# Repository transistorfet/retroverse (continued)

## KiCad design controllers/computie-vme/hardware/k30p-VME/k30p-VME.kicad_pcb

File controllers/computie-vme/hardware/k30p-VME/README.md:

k30p-VME
========

Status: In Design

Latest: Unreleased

### About

A CPU card for a VME-based computer system using an MC68030 with some onboard RAM and Flash, and a
onboard serial ports with integrated FTDI Serial-to-USB controllers, and a programmable ATF1508
CPLD for glue logic.  The 'p' in the name stands for Programmable due to the CPLD.

Currently it's in development and I'm making slow progress with the CPLD, but I don't want to jump
further ahead until I'm sure I can make it work

Parts
-----

- MC68681
    - eBay, AliExpress, or other resellers are the only sources for these chips
- MC68030RC or MC68030RP:
    - eBay, AliExpress, or other resellers are the only sources for these chips

- 128-pin 13x13 PGA Socket
    - Phoenix Enterprise Connectors: https://www.peconnectors.com/sockets-pga-cpu-and-memory/hws4514/
    - Digikey: https://www.digikey.ca/en/products/detail/mill-max-manufacturing-corp/510-43-128-13-041001/7753825
    - Mouser: https://www.mouser.ca/ProductDetail/Aries-Electronics/128-PGM13039-10
    - (Not sure if correct pin arrangement) https://www.mouser.ca/ProductDetail/Preci-dip/510-87-128-13-041101

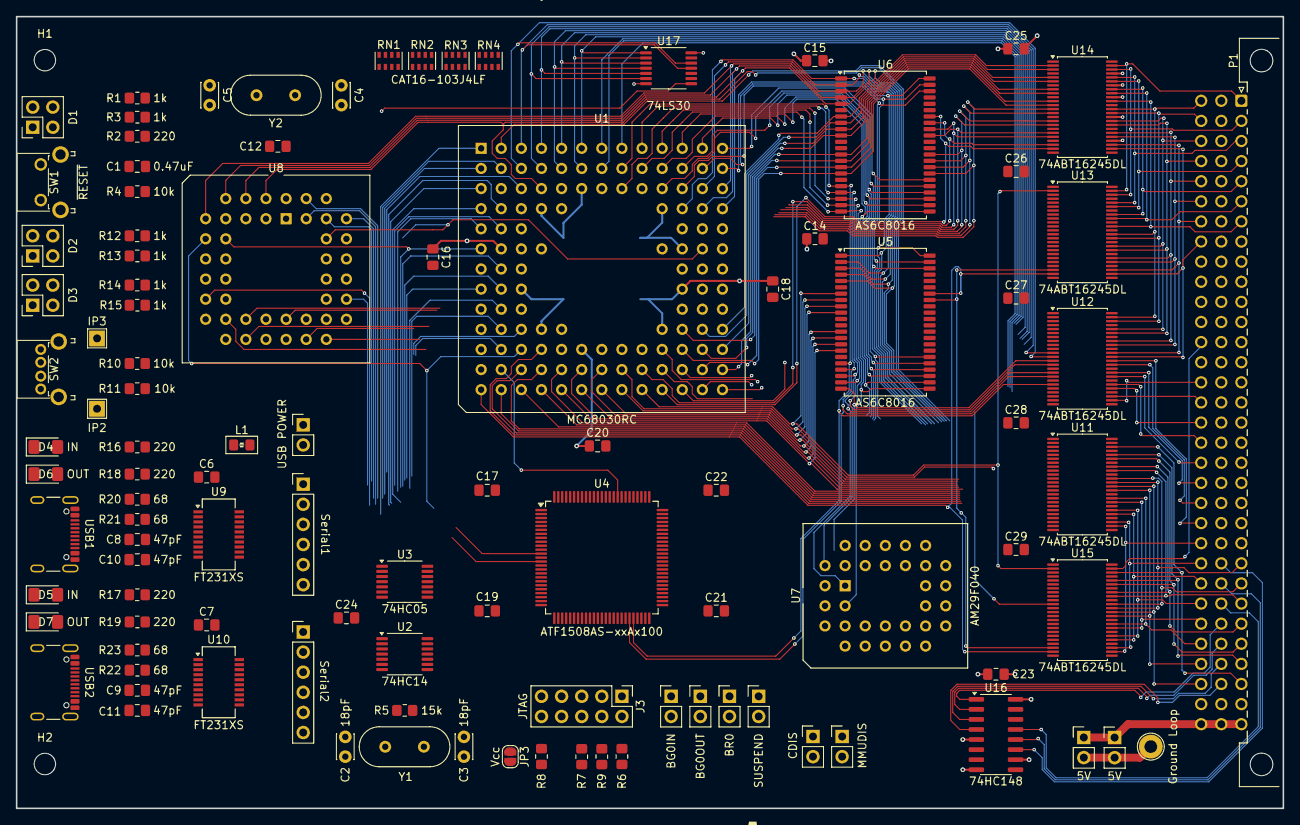
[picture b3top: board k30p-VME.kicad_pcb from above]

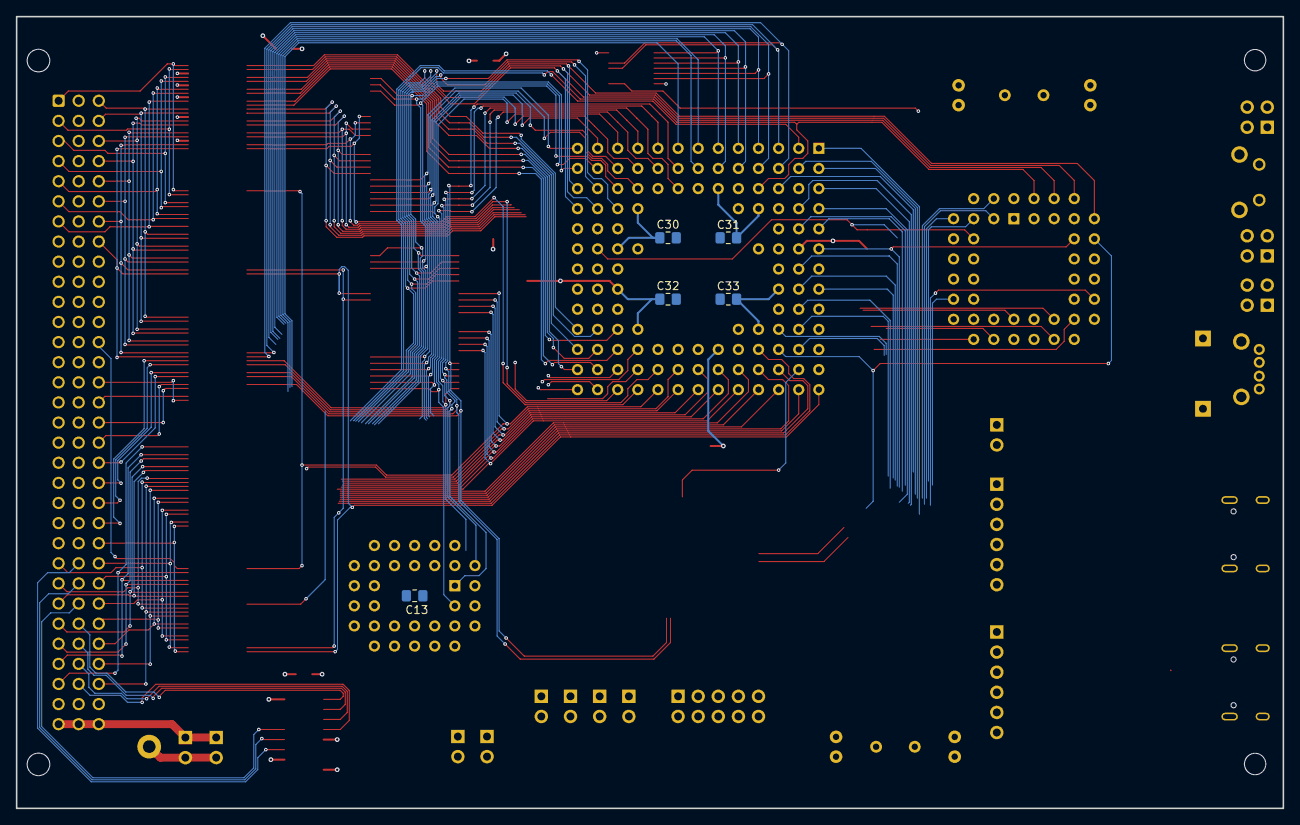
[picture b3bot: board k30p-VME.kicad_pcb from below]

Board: 4 copper layers, 160.0 x 100.0 mm, 111 parts (5 on the bottom side), 245 nets.

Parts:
C1: 0.47uF; C_0805_2012Metric_Pad1.18x1.45mm_HandSolder
C2, C3: 18pF; C_Disc_D3.0mm_W2.0mm_P2.50mm
C4: 15pF; C_Disc_D3.0mm_W2.0mm_P2.50mm
C5: 5pF; C_Disc_D3.0mm_W2.0mm_P2.50mm
C6, C7, C12, C13, C14, C15, C16, C17, C18, C19, C20, C21, C22, C23, C24, C25, C26, C27, C28, C29, C30, C31, C32, C33: 0.1uF; C_0805_2012Metric_Pad1.18x1.45mm_HandSolder
C8, C9, C10, C11: 47pF; C_0805_2012Metric_Pad1.18x1.45mm_HandSolder
D1: Harvatek HV-32H307B; Harvatek_HV-32312-260-2SUB
D2, D3: Harvatek HV-32312; Harvatek_HV-32312-260-2SUB
D4, D5: IN; LED_1206_3216Metric_Pad1.42x1.75mm_HandSolder
D6, D7: OUT; LED_1206_3216Metric_Pad1.42x1.75mm_HandSolder
H1, H2: MountingHole; MountingHole_2.7mm_M2.5_DIN965
J1, J2: 5V; PinHeader_1x02_P2.54mm_Vertical
J3: JTAG; PinHeader_2x05_P2.54mm_Vertical
J4: Serial1; PinHeader_1x06_P2.54mm_Vertical
J5: Serial2; PinHeader_1x06_P2.54mm_Vertical
JP1: CDIS; PinHeader_1x02_P2.54mm_Vertical
JP2: MMUDIS; PinHeader_1x02_P2.54mm_Vertical
JP3: Vcc; SolderJumper-2_P1.3mm_Open_RoundedPad1.0x1.5mm
JP4: USB POWER; PinHeader_1x02_P2.54mm_Vertical
JP5: BG0IN; PinHeader_1x02_P2.54mm_Vertical
JP6: BG0OUT; PinHeader_1x02_P2.54mm_Vertical
JP7: BR0; PinHeader_1x02_P2.54mm_Vertical
JP8: SUSPEND; PinHeader_1x02_P2.54mm_Vertical
L1: MI0805K601R-10; Ferrite_0805_2012Metric_Pad1.15x1.40mm_BigPads
P1: VME64-P1-3R; DIN41612_C_3x32_Male_Horizontal_THT
R1, R3, R12, R13, R14, R15: 1k; R_0805_2012Metric_Pad1.20x1.40mm_HandSolder
R2, R16, R17, R18, R19: 220; R_0805_2012Metric_Pad1.20x1.40mm_HandSolder
R4, R9, R10, R11: 10k; R_0805_2012Metric_Pad1.20x1.40mm_HandSolder
R5: 15k; R_0805_2012Metric_Pad1.20x1.40mm_HandSolder
R6, R7, R8: 4.7k; R_0805_2012Metric_Pad1.20x1.40mm_HandSolder
R20, R21, R22, R23: 68; R_0805_2012Metric_Pad1.20x1.40mm_HandSolder
RN1, RN2, RN3, RN4: CAT16-103J4LF; R_Cat16-4
S1: Logo_Open_Hardware_Small; OSHW-Symbol_6.7x6mm_SilkScreen
SW1: ~{RESET}; E-Switch_TL1105
SW2: E-Switch TL2243; E-Switch_TL2243
TP1: Ground Loop; TestPoint_Loop_D2.60mm_Drill1.6mm_Beaded
TP5: IP3; TestPoint_THTPad_2.0x2.0mm_Drill1.0mm
TP6: IP2; TestPoint_THTPad_2.0x2.0mm_Drill1.0mm
U1: MC68030RC; PGA-128_13x13_THT-Socket
U2: 74HC14; TSSOP-14_4.4x5mm_P0.65mm
U3: 74HC05; TSSOP-14_4.4x5mm_P0.65mm
U4: ATF1508AS-xxAx100; TQFP-100_14x14mm_P0.5mm
U5, U6: AS6C8016; TSOP-II-44_10.16x18.41mm_P0.8mm
U7: AM29F040; PLCC-32_THT-Socket
U8: MC68681; PLCC-44_THT-Socket
U9, U10: FT231XS; SSOP-20_3.9x8.7mm_P0.635mm
U11, U12, U13, U14, U15: 74ABT16245DL; TSSOP-48_6.1x12.5mm_P0.5mm
U16: 74HC148; SOIC-16_3.9x9.9mm_P1.27mm
U17: 74LS30; TSSOP-14_4.4x5mm_P0.65mm
USB1, USB2: USB_C_Plug_USB2.0; USB_C_Receptacle_GCT_USB4105-xx-A_16P_TopMnt_Horizontal
Y1, Y2: Crystal; Crystal_HC49-4H_Vertical

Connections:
+5V: C12.1, C13.1, C14.1, C15.1, C16.1, C17.1, C18.1, C19.1, C20.1, C21.1, C22.1, C23.1, C24.1, C25.1, C26.1, C27.1, C28.1, C29.1, C30.1, C31.1, C32.1, C33.1, J1.1, J2.1, JP3.2 (B), JP4.1 (A), P1.a32 (+5V), P1.b32 (+5V), P1.c32 (+5V), R1.2, R4.1, R6.1, R7.1, R8.1, R9.1, R12.2, R13.2, R14.2, R15.2, RN1.5 (R4.2), RN1.6 (R3.2), RN1.7 (R2.2), RN1.8 (R1.2), RN2.5 (R4.2), RN2.6 (R3.2), RN2.7 (R2.2), RN2.8 (R1.2), RN3.5 (R4.2), RN3.6 (R3.2), RN3.7 (R2.2), RN3.8 (R1.2), RN4.5 (R4.2), RN4.6 (R3.2), RN4.7 (R2.2), RN4.8 (R1.2), SW2.2 (D), SW2.4 (D), U1.C6 (VCC), U1.D4 (VCC), U1.D10 (VCC), U1.F2 (VCC), U1.F11 (VCC), U1.H3 (VCC), U1.H11 (VCC), U1.K4 (VCC), U1.K10 (VCC), U1.L6 (VCC), U2.14 (VCC), U3.14 (VCC), U4.3 (VCCIO), U4.18 (VCCIO), U4.34 (VCCIO), U4.39 (VCCINT), U4.51 (VCCIO), U4.66 (VCCIO), U4.82 (VCCIO), U4.91 (VCCINT), U5.11 (VCC), U5.33 (VCC), U6.11 (VCC), U6.33 (VCC), U7.32 (VCC), U8.44 (VCC), U9.15 (VCC), U10.15 (VCC), U11.7 (VCC), U11.18 (VCC), U11.31 (VCC), U11.42 (VCC), U12.7 (VCC), U12.18 (VCC), U12.31 (VCC), U12.42 (VCC), U13.7 (VCC), U13.18 (VCC), U13.31 (VCC), U13.42 (VCC), U14.7 (VCC), U14.18 (VCC), U14.31 (VCC), U14.42 (VCC), U15.7 (VCC), U15.18 (VCC), U15.31 (VCC), U15.42 (VCC), U16.16 (VCC), U17.14 (VCC)
CPU_CLK: U1.E1 (CLK), U4.83 (I/O)
D16X_DIR: U4.94 (I/O), U13.1 (DIR1), U13.24 (DIR2)
DL_DIR: U4.97 (I/O), U14.1 (DIR1), U14.24 (DIR2)
FC0: U1.D2 (FC0), U4.12 (I/O)
FC1: U1.C1 (FC1), U4.13 (I/O)
FC2: U1.D1 (FC2), U4.14 (I/O)
GND: C1.2, C2.2, C3.2, C4.1, C5.1, C6.2, C7.2, C8.2, C9.2, C10.2, C11.2, C12.2, C13.2, C14.2, C15.2, C16.2, C17.2, C18.2, C19.2, C20.2, C21.2, C22.2, C23.2, C24.2, C25.2, C26.2, C27.2, C28.2, C29.2, C30.2, C31.2, C32.2, C33.2, J1.2, J2.2, J3.2, J3.10, J4.6, J5.1, JP1.2 (B), JP2.2 (B), JP8.2 (B), P1.a9 (GND), P1.a11 (GND), P1.a15 (GND), P1.a17 (GND), P1.a19 (GND), P1.b20 (GND), P1.b23 (GND), P1.c9 (GND), R2.1, R3.1, R10.2, R11.2, SW1.1, TP1.1, U1.C5 (GND), U1.C7 (GND), U1.C9 (GND), U1.E3 (GND), U1.E11 (GND), U1.F3 (GND), U1.G3 (GND), U1.G11 (GND), U1.J3 (GND), U1.J11 (GND), U1.L5 (GND), U1.L7 (GND), U1.L8 (GND), U1.L9 (GND), U2.7 (GND), U3.7 (GND), U4.11 (GND), U4.26 (GND), U4.38 (GND), U4.43 (GND), U4.59 (GND), U4.74 (GND), U4.86 (GND), U4.95 (GND), U5.12 (VSS), U5.34 (VSS), U6.12 (VSS), U6.34 (VSS), U7.16 (GND), U8.22 (GND), U9.6 (GND), U9.16 (GND), U10.6 (GND), U10.16 (GND), U11.1 (DIR1), U11.4 (GND), U11.10 (GND), U11.15 (GND), U11.21 (GND), U11.24 (DIR2), U11.28 (GND), U11.34 (GND), U11.39 (GND), U11.45 (GND), U12.1 (DIR1), U12.4 (GND), U12.10 (GND), U12.15 (GND), U12.21 (GND), U12.24 (DIR2), U12.28 (GND), U12.34 (GND), U12.39 (GND), U12.45 (GND), U13.4 (GND), U13.10 (GND), U13.15 (GND), U13.21 (GND), U13.28 (GND), U13.34 (GND), U13.39 (GND), U13.45 (GND), U14.4 (GND), U14.10 (GND), U14.15 (GND), U14.21 (GND), U14.28 (GND), U14.34 (GND), U14.39 (GND), U14.45 (GND), U15.4 (GND), U15.10 (GND), U15.15 (GND), U15.21 (GND), U15.28 (GND), U15.34 (GND), U15.39 (GND), U15.45 (GND), U16.5 (EI), U16.8 (GND), U16.10 (IO), U17.7 (GND), USB1.A1 (GND), USB1.A12 (GND), USB1.B1 (GND), USB1.B12 (GND), USB1.S1 (SHIELD), USB2.A1 (GND), USB2.A12 (GND), USB2.B1 (GND), USB2.B12 (GND), USB2.S1 (SHIELD)
IP4: U4.54 (I/O), U8.43 (IP4)
IP5: U4.53 (I/O), U8.42 (IP5)
LA0: U1.A2 (A0), U4.35 (I/O), U7.12 (A0)
LA1: U1.C4 (A1), U4.36 (I/O), U7.11 (A1), U8.2 (RS1), U11.3 (B1)
LA2: U1.D13 (A2), U4.37 (I/O), U5.5 (A0), U6.5 (A0), U7.10 (A2), U8.4 (RS2), U11.5 (B2)
LA3: U1.D12 (A3), U4.40 (I/O), U5.4 (A1), U6.4 (A1), U7.9 (A3), U8.6 (RS3), U11.6 (B3)
LA4: U1.C13 (A4), U5.3 (A2), U6.3 (A2), U7.8 (A4), U8.7 (RS4), U11.8 (B4)
LA5: U1.C12 (A5), U5.2 (A3), U6.2 (A3), U7.7 (A5), U11.9 (B5)
LA6: U1.D11 (A6), U5.1 (A4), U6.1 (A4), U7.6 (A6), U11.11 (B6)
LA7: U1.B13 (A7), U5.44 (A5), U6.44 (A5), U7.5 (A7), U11.12 (B7)
LA8: U1.B12 (A8), U5.43 (A6), U6.43 (A6), U7.27 (A8), U11.13 (B8)
LA9: U1.C11 (A9), U5.42 (A7), U6.42 (A7), U7.26 (A9), U11.14 (B9)
LA10: U1.A13 (A10), U5.28 (A8), U6.28 (A8), U7.23 (A10), U11.16 (B10)
LA11: U1.C10 (A11), U5.27 (A9), U6.27 (A9), U7.25 (A11), U11.17 (B11)
LA12: U1.B11 (A12), U5.26 (A10), U6.26 (A10), U7.4 (A12), U11.19 (B12)
LA13: U1.A12 (A13), U5.25 (A11), U6.25 (A11), U7.28 (A13), U11.20 (B13)
LA14: U1.B10 (A14), U5.24 (A12), U6.24 (A12), U7.29 (A14), U11.22 (B14)
LA15: U1.A11 (A15), U5.23 (A13), U6.23 (A13), U7.3 (A15), U11.23 (B15)
LA16: U1.B9 (A16), U4.41 (I/O/PD2), U5.22 (A14), U6.22 (A14), U7.2 (A16), U12.13 (B8)
LA17: U1.A10 (A17), U4.42 (I/O), U5.21 (A15), U6.21 (A15), U7.30 (A17), U12.14 (B9)
LA18: U1.C8 (A18), U4.44 (I/O), U5.20 (A16), U6.20 (A16), U7.1 (A18), U12.16 (B10)
LA19: U1.A9 (A19), U4.45 (I/O), U5.19 (A17), U6.19 (A17), U12.17 (B11)
LA20: U1.B8 (A20), U4.46 (I/O), U5.18 (A18), U6.18 (A18), U12.19 (B12)
LA21: U1.A8 (A21), U4.47 (I/O), U12.20 (B13)
LA22: U1.B7 (A22), U4.48 (I/O), U12.22 (B14)
LA23: U1.A7 (A23), U4.49 (I/O), U12.23 (B15)
LA24: U1.A6 (A24), U12.2 (B0), U17.1
LA25: U1.B6 (A25), U12.3 (B1), U17.2
LA26: U1.A5 (A26), U12.5 (B2), U17.3
LA27: U1.B5 (A27), U12.6 (B3), U17.4
LA28: U1.A4 (A28), U12.8 (B4), U17.5
LA29: U1.B4 (A29), U12.9 (B5), U17.6
LA30: U1.A3 (A30), U12.11 (B6), U17.11
LA31: U1.B3 (A31), U12.12 (B7), U17.12
LD0: U1.K13 (D0), U6.7 (Q0), U14.2 (B0)
LD1: U1.K12 (D1), U6.8 (Q1), U14.3 (B1)
LD2: U1.L13 (D2), U6.9 (Q2), U14.5 (B2)
LD3: U1.M13 (D3), U6.10 (Q3), U14.6 (B3)
LD4: U1.L12 (D4), U6.13 (Q4), U14.8 (B4)
LD5: U1.K11 (D5), U6.14 (Q5), U14.9 (B5)
LD6: U1.M12 (D6), U6.15 (Q6), U14.11 (B6)
LD7: U1.L11 (D7), U6.16 (Q7), U14.12 (B7)
LD8: U1.N13 (D8), U6.29 (Q8), U14.13 (B8)
LD9: U1.M11 (D9), U6.30 (Q9), U14.14 (B9)
LD10: U1.L10 (D10), U6.31 (Q10), U14.16 (B10)
LD11: U1.N12 (D11), U6.32 (Q11), U14.17 (B11)
LD12: U1.M10 (D12), U6.35 (Q12), U14.19 (B12)
LD13: U1.N11 (D13), U6.36 (Q13), U14.20 (B13)
LD14: U1.M9 (D14), U6.37 (Q14), U14.22 (B14)
LD15: U1.N10 (D15), U6.38 (Q15), U14.23 (B15)
LD16: U1.N9 (D16), U5.7 (Q0), U13.2 (B0), U15.2 (B0)
LD17: U1.M8 (D17), U5.8 (Q1), U13.3 (B1), U15.3 (B1)
LD18: U1.N8 (D18), U5.9 (Q2), U13.5 (B2), U15.5 (B2)
LD19: U1.N7 (D19), U5.10 (Q3), U13.6 (B3), U15.6 (B3)
LD20: U1.M7 (D20), U5.13 (Q4), U13.8 (B4), U15.8 (B4)
LD21: U1.N6 (D21), U5.14 (Q5), U13.9 (B5), U15.9 (B5)
LD22: U1.M6 (D22), U5.15 (Q6), U13.11 (B6), U15.11 (B6)
LD23: U1.N5 (D23), U5.16 (Q7), U13.12 (B7), U15.12 (B7)
LD24: U1.M5 (D24), U5.29 (Q8), U7.13 (Q0), U8.28 (D0), U13.13 (B8), U15.13 (B8)
LD25: U1.N4 (D25), U5.30 (Q9), U7.14 (Q1), U8.18 (D1), U13.14 (B9), U15.14 (B9)
LD26: U1.N3 (D26), U5.31 (Q10), U7.15 (Q2), U8.27 (D2), U13.16 (B10), U15.16 (B10)
LD27: U1.M4 (D27), U5.32 (Q11), U7.17 (Q3), U8.19 (D3), U13.17 (B11), U15.17 (B11)
LD28: U1.N2 (D28), U5.35 (Q12), U7.18 (Q4), U8.26 (D4), U13.19 (B12), U15.19 (B12)
LD29: U1.M3 (D29), U5.36 (Q13), U7.19 (Q5), U8.20 (D5), U13.20 (B13), U15.20 (B13)
LD30: U1.L4 (D30), U5.37 (Q14), U7.20 (Q6), U8.25 (D6), U13.22 (B14), U15.22 (B14)
LD31: U1.N1 (D31), U5.38 (Q15), U7.21 (Q7), U8.21 (D7), U13.23 (B15), U15.23 (B15)
MAIN_CLK: U2.6, U4.87 (I/GCLK1)
MD32X_DIR: U4.92 (I/O), U15.1 (DIR1), U15.24 (DIR2)
unnamed: C1.1, R4.2, SW1.2, U2.13
unnamed: C2.1, R5.2, U2.3, Y1.1
unnamed: C3.1, R5.1, U2.4, U2.5, Y1.2
unnamed: D1.2 (K1), R3.2
unnamed: D1.4 (K2), R2.2
unnamed: D2.1 (A1), R13.1
unnamed: D2.3 (A2), R12.1
unnamed: D2.2 (K1), U8.16 (OP5)
unnamed: D2.4 (K2), U8.30 (OP4)
unnamed: D3.1 (A1), R15.1
unnamed: D3.3 (A2), R14.1
unnamed: D3.2 (K1), U8.17 (OP7)
unnamed: D3.4 (K2), U8.29 (OP6)
unnamed: D4.2 (A), R16.2
unnamed: D4.1 (K), U9.10 (CBUS2)
unnamed: D5.2 (A), R17.2
unnamed: D5.1 (K), U10.10 (CBUS2)
unnamed: D6.2 (A), R18.2
unnamed: D6.1 (K), U9.17 (CBUS1)
unnamed: D7.2 (A), R19.2
unnamed: D7.1 (K), U10.17 (CBUS1)
unnamed: J3.4, JP3.1 (A)
unnamed: JP4.2 (B), L1.2
unnamed: P1.a21 (~IACKIN), P1.a22 (~IACKOUT)
unnamed: P1.a20 (~IACK), U3.12
unnamed: P1.b30 (~IRQ1), U16.4 (I7)
unnamed: P1.b29 (~IRQ2), U16.3 (I6)
unnamed: P1.b28 (~IRQ3), U16.2 (I5)
unnamed: P1.b27 (~IRQ4), U16.1 (I4)
unnamed: P1.b26 (~IRQ5), U16.13 (I3)
unnamed: P1.b25 (~IRQ6), U16.12 (I2)
unnamed: P1.b24 (~IRQ7), U16.11 (I1)
unnamed: RN2.2 (R2.1), U1.G1 (STERM)
unnamed: RN2.3 (R3.1), U1.J1 (CBACK)
unnamed: RN2.4 (R4.1), U1.L1 (CIIN)
unnamed: R11.1, SW2.1 (C), TP6.1, U8.40 (IP2)
unnamed: R10.1, SW2.3 (C), TP5.1, U8.3 (IP3)
unnamed: U2.8, U3.9
unnamed: U2.12, U3.1, U3.3
unnamed: C4.2, U8.36 (X1/CLK), Y2.2
unnamed: C5.2, U8.37 (X2), Y2.1
unnamed: C6.1, R16.1, R18.1, U9.3 (VCCIO), U9.13 (3V3OUT), U9.14 (~RESET)
unnamed: R20.2, U9.12 (USBDM)
unnamed: R21.2, U9.11 (USBDP)
unnamed: C7.1, R17.1, R19.1, U10.3 (VCCIO), U10.13 (3V3OUT), U10.14 (~RESET)
unnamed: R22.2, U10.12 (USBDM)
unnamed: R23.2, U10.11 (USBDP)
unnamed: U4.50 (I/O), U17.8
OP2: U4.56 (I/O), U8.31 (OP2)
OP3: U4.55 (I/O), U8.15 (OP3)
SIZ0: U1.L2 (SIZ0), U4.5 (I/O)
SIZ1: U1.K3 (SIZ1), U4.6 (I/O)
STATUSLED: D1.3 (A2), U4.52 (I/O)
TCK: J3.1, R6.2, U4.62 (I/O/TCK)
TDI: J3.9, R8.2, U4.4 (I/O/TDI)
TDO: J3.3, R9.2, U4.73 (I/O/TDO)
TMS: J3.5, R7.2, U4.15 (I/O/TMS)
UART1_CTS: J4.5, U8.32 (OP0), U9.9 (~CTS)
UART1_DTR: J4.1, U8.8 (IP0), U9.1 (~DTR)
UART1_RX: J4.2, U8.33 (TXDA), U9.4 (RXD)
UART1_TX: J4.3, U8.35 (RXDA), U9.20 (TXD)
UART2_CTS: J5.2, U8.14 (OP1), U10.9 (~CTS)
UART2_DTR: J5.6, U8.5 (IP1), U10.1 (~DTR)
UART2_RX: J5.5, U8.13 (TXDB), U10.4 (RXD)
UART2_TX: J5.4, U8.11 (RXDB), U10.20 (TXD)
USB1_5V: J4.4, L1.1, USB1.A4 (VBUS), USB1.A9 (VBUS), USB1.B4 (VBUS), USB1.B9 (VBUS)
USB1_DN: C8.1, R20.1, USB1.A7 (D-)
USB1_DP: C10.1, R21.1, USB1.A6 (D+)
USB2_DN: C9.1, R22.1, USB2.A7 (D-)
USB2_DP: C11.1, R23.1, USB2.A6 (D+)
VA1: P1.a30 (A01), U11.46 (A1), U15.46 (A1)
VA2: P1.a29 (A02), U11.44 (A2), U15.44 (A2)
VA3: P1.a28 (A03), U11.43 (A3), U15.43 (A3)
VA4: P1.a27 (A04), U11.41 (A4), U15.41 (A4)
VA5: P1.a26 (A05), U11.40 (A5), U15.40 (A5)
VA6: P1.a25 (A06), U11.38 (A6), U15.38 (A6)
VA7: P1.a24 (A07), U11.37 (A7), U15.37 (A7)
VA8: P1.c30 (A8), U11.36 (A8), U15.36 (A8)
VA9: P1.c29 (A9), U11.35 (A9), U15.35 (A9)
VA10: P1.c28 (A10), U11.33 (A10), U15.33 (A10)
VA11: P1.c27 (A11), U11.32 (A11), U15.32 (A11)
VA12: P1.c26 (A12), U11.30 (A12), U15.30 (A12)
VA13: P1.c25 (A13), U11.29 (A13), U15.29 (A13)
VA14: P1.c24 (A14), U11.27 (A14), U15.27 (A14)
VA15: P1.c23 (A15), U11.26 (A15), U15.26 (A15)
VA16: P1.c22 (A16), U12.36 (A8)
VA17: P1.c21 (A17), U12.35 (A9)
VA18: P1.c20 (A18), U12.33 (A10)
VA19: P1.c19 (A19), U12.32 (A11)
VA20: P1.c18 (A20), U12.30 (A12)
VA21: P1.c17 (A21), U12.29 (A13)
VA22: P1.c16 (A22), U12.27 (A14)
VA23: P1.c15 (A23), U12.26 (A15)
VAM0: P1.b16 (AM0), U4.72 (I/O)
VAM1: P1.b17 (AM1), U4.71 (I/O)
VAM2: P1.b18 (AM2), U4.70 (I/O)
VAM3: P1.b19 (AM3), U4.69 (I/O)
VAM4: P1.a23 (AM4), U4.68 (I/O)
VAM5: P1.c14 (AM5), U4.67 (I/O)
VD0: P1.a1 (D00), U13.47 (A0), U14.47 (A0)
VD1: P1.a2 (D01), U13.46 (A1), U14.46 (A1)
VD2: P1.a3 (D02), U13.44 (A2), U14.44 (A2)
VD3: P1.a4 (D03), U13.43 (A3), U14.43 (A3)
VD4: P1.a5 (D04), U13.41 (A4), U14.41 (A4)
VD5: P1.a6 (D05), U13.40 (A5), U14.40 (A5)
VD6: P1.a7 (D06), U13.38 (A6), U14.38 (A6)
VD7: P1.a8 (D07), U13.37 (A7), U14.37 (A7)
VD8: P1.c1 (D08), U12.47 (A0), U13.36 (A8), U14.36 (A8)
VD9: P1.c2 (D09), U12.46 (A1), U13.35 (A9), U14.35 (A9)
VD10: P1.c3 (D10), U12.44 (A2), U13.33 (A10), U14.33 (A10)
VD11: P1.c4 (D11), U12.43 (A3), U13.32 (A11), U14.32 (A11)
VD12: P1.c5 (D12), U12.41 (A4), U13.30 (A12), U14.30 (A12)
VD13: P1.c6 (D13), U12.40 (A5), U13.29 (A13), U14.29 (A13)
VD14: P1.c7 (D14), U12.38 (A6), U13.27 (A14), U14.27 (A14)
VD15: P1.c8 (D15), U12.37 (A7), U13.26 (A15), U14.26 (A15)
VSYSCLK: P1.a10 (SYSCLK), U4.90 (I/OE2/GCLK2)
~A40X_OE: U4.99 (I/O), U12.48 (~OE1)
~AL_OE: U4.100 (I/O), U11.25 (~OE2), U11.48 (~OE1), U12.25 (~OE2)
~AS: U1.J2 (AS), U4.1 (I/O/PD1)
~AVEC: RN1.2 (R2.1), U1.E2 (AVEC), U4.23 (I/O)
~BERR: RN1.3 (R3.1), U1.H1 (BERR), U4.10 (I/O)
~BGACK: RN1.1 (R1.1), U1.C3 (BGACK), U4.16 (I/O)
~BG: U1.B2 (BG), U4.17 (I/O)
~BR: JP8.1 (A), RN3.1 (R1.1), U1.A1 (BR), U4.19 (I/O)
~CDIS: JP1.1 (A), RN4.3 (R3.1), U1.H12 (CDIS)
~D16X_OE: U4.96 (I/O), U13.25 (~OE2), U13.48 (~OE1)
~DL_OE: U4.98 (I/O), U14.25 (~OE2), U14.48 (~OE1)
~DS0: U4.28 (I/O), U6.39 (~LB)
~DS1: U4.29 (I/O), U6.40 (~UB)
~DS2: U4.30 (I/O), U5.39 (~LB)
~DS3: U4.31 (I/O), U5.40 (~UB)
~DSACK0: RN1.4 (R4.1), U1.F1 (DSACK0), U4.8 (I/O), U8.10 (DTACK)
~DSACK1: RN2.1 (R1.1), U1.G2 (DSACK1), U4.9 (I/O)
~DS: U1.K2 (DS), U4.2 (I/O)
~ECS: U1.M2 (ECS), U4.84 (I/O)
~HALT: D1.1 (A1), R1.1, U1.H2 (HALT), U3.2
~IOSEL: U4.27 (I/O), U8.39 (CS)
~IPL0: RN3.3 (R3.1), U1.H13 (IPL0), U4.20 (I/O)
~IPL1: RN3.4 (R4.1), U1.G13 (IPL1), U4.21 (I/O)
~IPL2: RN4.1 (R1.1), U1.G12 (IPL2), U4.22 (I/O)
~MD32X_OE: U4.93 (I/O), U15.25 (~OE2), U15.48 (~OE1)
~MMUDIS: JP2.1 (A), RN4.2 (R2.1), U1.F13 (MMUDIS)
~RAMSEL: U4.24 (I/O), U5.6 (~CE), U6.6 (~CE)
~RD: U2.2, U5.41 (~OE), U6.41 (~OE), U7.24 (~OE)
~RESET: RN3.2 (R2.1), U1.F12 (RESET), U3.4, U3.8, U4.89 (I/GCLR), U8.38 (RESET)
~RMC: U1.B1 (RMC), U4.88 (I/OE1)
~ROMSEL: U4.25 (I/O), U7.22 (~CS)
~SIACK: U4.33 (I/O), U8.41 (IACK)
~SIRQ: U4.32 (I/O), U8.24 (IRQ)
~VAS: P1.a18 (~AS), U4.81 (I/O)
~VBBSY: P1.b1 (~BBSY), U4.85 (I/O/GCLK3)
~VBERR: P1.c11 (~BERR), U4.75 (I/O)
~VBG0IN: JP5.2 (B), P1.b4 (~BG0IN)
~VBG0OUT: JP6.2 (B), P1.b5 (~BG0OUT)
~VBGIN: JP5.1 (A), U4.64 (I/O)
~VBGOUT: JP6.1 (A), U4.63 (I/O)
~VBR0: JP7.2 (B), P1.b12 (~BR0)
~VBR: JP7.1 (A), U4.65 (I/O)
~VDS0: P1.a13 (~DS0), U4.78 (I/O)
~VDS1: P1.a12 (~DS1), U4.79 (I/O)
~VDTACK: P1.a16 (~DTACK), U4.76 (I/O)
~VIACK: U3.13, U4.57 (I/O)
~VIPL0: U4.61 (I/O), U16.9 (S0)
~VIPL1: U4.60 (I/O), U16.7 (S1)
~VIPL2: U4.58 (I/O), U16.6 (S2)
~VLWORD: P1.c13 (~LWORD), U4.80 (I/O), U15.47 (A0)
~VSYSRESET: P1.c12 (~SYSRESET), U2.9
~VWRITE: P1.a14 (~WRITE), U4.77 (I/O)
~WR: U1.L3 (R/W), U2.1, U4.7 (I/O), U5.17 (~WE), U6.17 (~WE), U7.31 (~WE), U8.9 (R/W)
